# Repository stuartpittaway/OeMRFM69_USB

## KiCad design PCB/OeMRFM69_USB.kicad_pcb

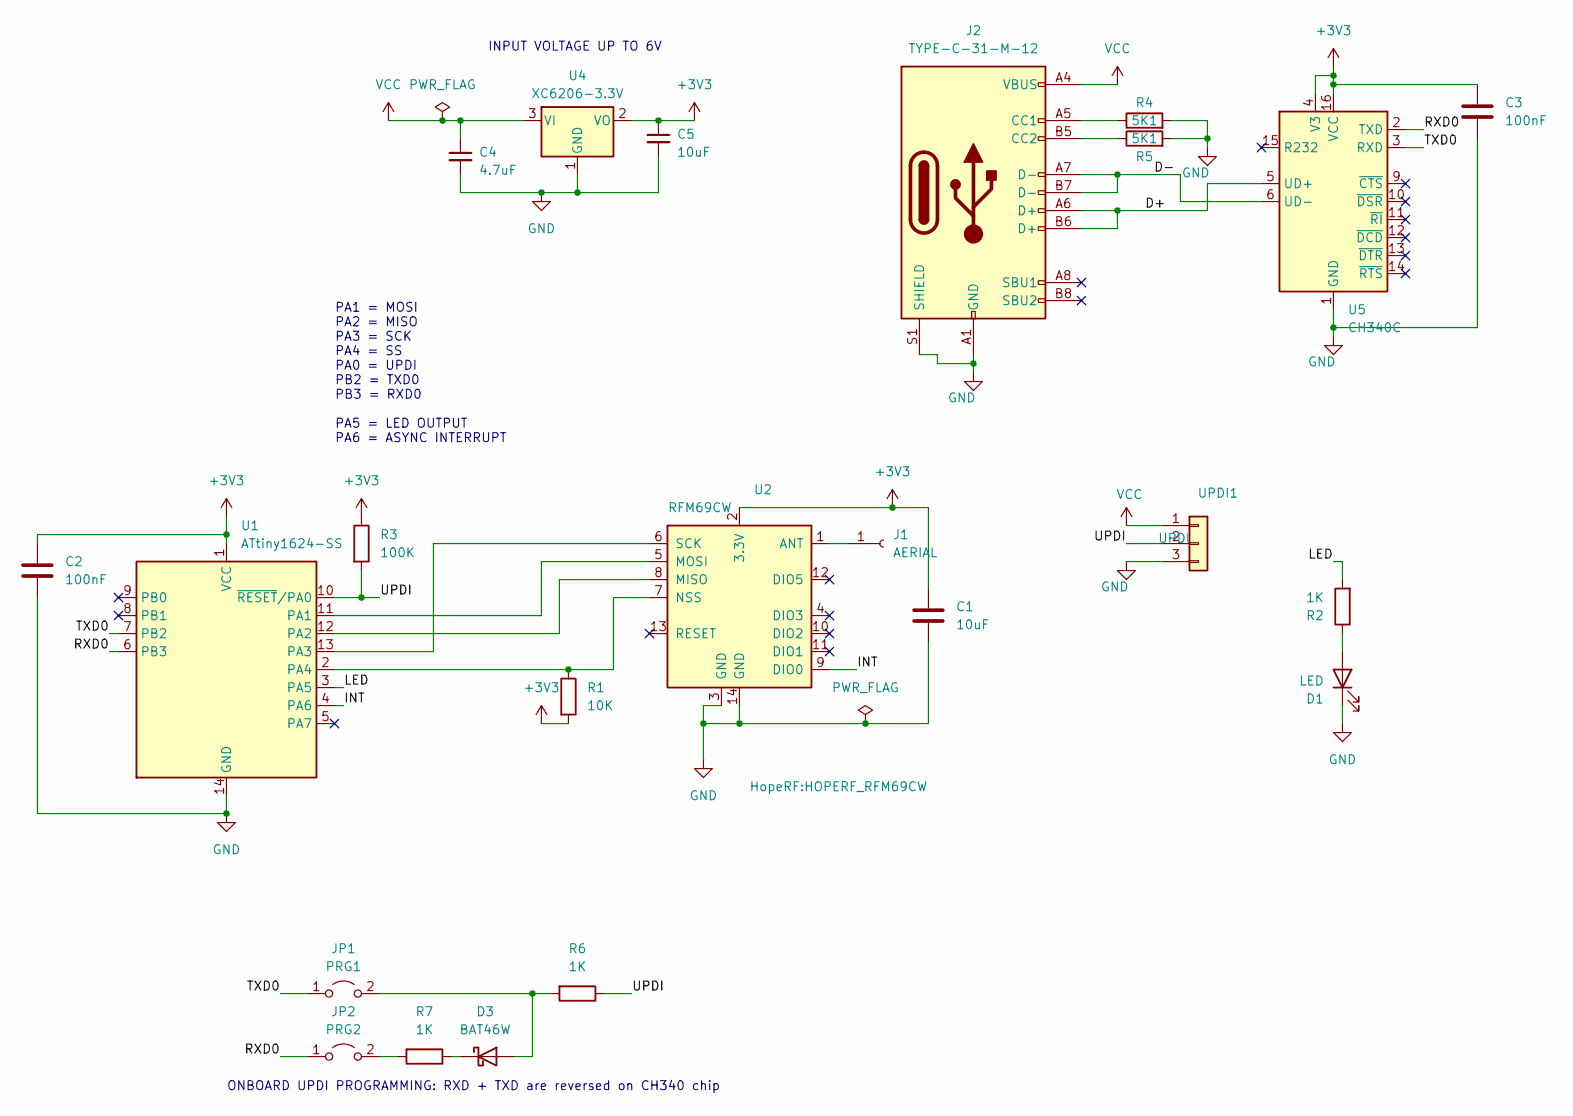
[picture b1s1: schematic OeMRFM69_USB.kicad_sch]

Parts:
C1, C5: 10uF; C_0805_2012Metric; PartNumber CL21A106KAYNNNE; LCSCStockCode C15850
C2, C3: 100nF; C_0805_2012Metric; PartNumber CC0805KRX7R9BB104; LCSCStockCode C49678
C4: 4.7uF; C_0805_2012Metric; PartNumber CL21A475KAQNNNE; LCSCStockCode C1779
D1: LED; LED_0805_2012Metric; PartNumber NCD0805R1; LCSCStockCode C84256
D3: BAT46W; D_SOD-123; PartNumber BAT46W; LCSCStockCode C54110
J1: AERIAL; PinHeader_1x01_P2.54mm_Vertical
J2: TYPE-C-31-M-12; PartNumber TYPE-C-31-M-12; LCSCStockCode C165948
JP1: PRG1; PinHeader_1x02_P2.54mm_Vertical; PartNumber KH-A2541WV-2P; LCSCStockCode C2833329
JP2: PRG2; PinHeader_1x02_P2.54mm_Vertical; PartNumber KH-A2541WV-2P; LCSCStockCode C2833329
R1: 10K; R_0805_2012Metric; PartNumber 0805W8F1002T5E; LCSCStockCode C17414
R2, R6, R7: 1K; R_0805_2012Metric; PartNumber 0805W8F1001T5E; LCSCStockCode C17513
R3: 100K; R_0805_2012Metric; PartNumber 0805W8F1003T5E; LCSCStockCode C149504
R4, R5: 5K1; R_0805_2012Metric; PartNumber 0805W8F5101T5E; LCSCStockCode C27834
U1: ATtiny1624-SS; SOIC-14_3.9x8.7mm_P1.27mm; PartNumber ATTINY1624-SS; LCSCStockCode C5160891
U2: RFM69CW; HOPERF_RFM69CW
U4: XC6206-3.3V; SOT-23-3; PartNumber XC6206-3.3V; LCSCStockCode C2891841
U5: CH340C; SOIC-16_3.9x9.9mm_P1.27mm; PartNumber CH340C; LCSCStockCode C84681
UPDI1: UPDI; PinSocket_1x03_P2.54mm_Vertical

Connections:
+3V3: C1.1, C2.1, C3.1, C5.1, R1.2, R3.1, U1.1 (VCC), U2.2 (3.3V), U4.2 (VO), U5.4 (V3), U5.16 (VCC)
/D+: J2.A6 (D+), J2.B6 (D+), U5.5 (UD+)
/D-: J2.A7 (D-), J2.B7 (D-), U5.6 (UD-)
/INT: U1.4 (PA6), U2.9 (DIO0)
/LED: R2.2, U1.3 (PA5)
/RXD0: JP2.1 (A), U1.6 (PB3), U5.2 (TXD)
/TXD0: JP1.1 (A), U1.7 (PB2), U5.3 (RXD)
/UPDI: R3.2, R6.1, U1.10 (~RESET/PA0), UPDI1.2
GND: C1.2, C2.2, C3.2, C4.2, C5.2, D1.1 (K), J2.A1 (GND), J2.A12 (GND), J2.B1 (GND), J2.B12 (GND), J2.S1 (SHIELD), R4.2, R5.2, U1.14 (GND), U2.3 (GND), U2.14 (GND), U4.1 (GND), U5.1 (GND), UPDI1.3
unnamed: D1.2 (A), R2.1
unnamed: D3.2 (A), JP1.2 (B), R6.2
unnamed: D3.1 (K), R7.1
unnamed: J1.1, U2.1 (ANT)
unnamed: J2.A5 (CC1), R4.1
unnamed: J2.B5 (CC2), R5.1
unnamed: JP2.2 (B), R7.2
unnamed: U1.11 (PA1), U2.5 (MOSI)
unnamed: U1.12 (PA2), U2.8 (MISO)
unnamed: U1.13 (PA3), U2.6 (SCK)
unnamed: R1.1, U1.2 (PA4), U2.7 (NSS)
VCC: C4.1, J2.A4 (VBUS), J2.A9 (VBUS), J2.B4 (VBUS), J2.B9 (VBUS), U4.3 (VI), UPDI1.1

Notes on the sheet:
ONBOARD UPDI PROGRAMMING: RXD + TXD are reversed on CH340 chip
PA1 = MOSI PA2 = MISO PA3 = SCK PA4 = SS PA0 = UPDI PB2 = TXD0 PB3 = RXD0 PA5 = LED OUTPUT PA6 = ASYNC INTERRUPT
INPUT VOLTAGE UP TO 6V

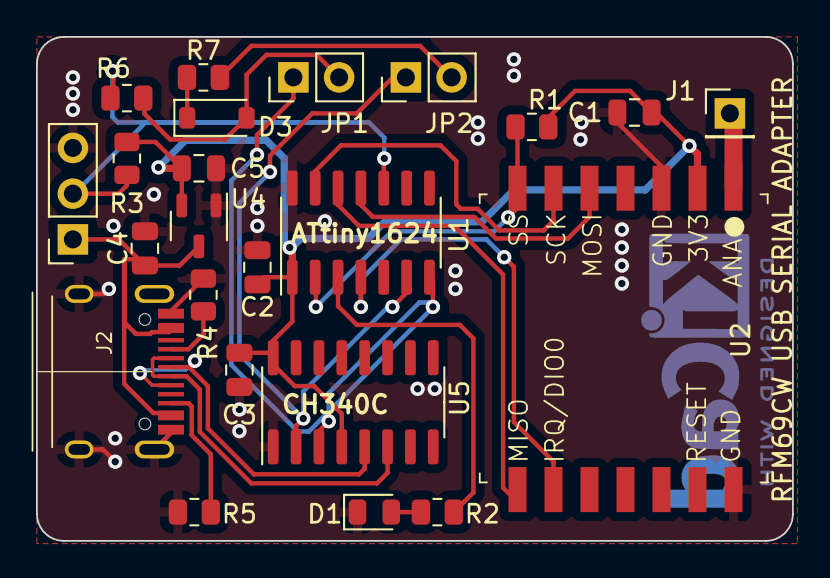
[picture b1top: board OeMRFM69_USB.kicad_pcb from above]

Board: 2 copper layers, 42.0 x 28.0 mm, 23 parts (0 on the bottom side), 21 nets.

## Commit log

2023-08-01 First check in
2023-08-01 Add hash silkscreen stamp
2023-08-01 Upload artifacts
2023-08-01 Updated BOM
2023-08-30 RFM69 footprint changes
2023-12-05 Bump tj-actions/branch-names from 6 to 7.0.7 in /.github/workflows
    Bumps [tj-actions/branch-names](https://github.com/tj-actions/branch-names) from 6 to 7.0.7.
    - [Release notes](https://github.com/tj-actions/branch-names/releases)
    - [Changelog](https://github.com/tj-actions/branch-names/blob/main/HISTORY.md)
    - [Commits](https://github.com/tj-actions/branch-names/compare/v6...v7.0.7)
    ---
    updated-dependencies:
